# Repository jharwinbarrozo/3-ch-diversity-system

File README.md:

This is an Arduino code for a Wemos D1 board (ESP8266 chip), coupled to 3 LM1881 video sync separators, and a MAX4545 video switch.
Compared to the popular RSSI-based systems, the advantages a video-based diversity are:
- No need to open the receivers to get the RSSI [Receiver Signal Strength indication] signals. You just have to plug in your different receivers, and they can be of different types.
- There is no need to calibrate the RSSi signals of the different receivers (this is often the tricky part).
- It is also frequent to get a strongly distorted image, while the RSSI is high.
- When the reception level is low (flying far for instance), some receivers have RSSI close to zero, although the image is still viewable. In that case an RSSI-based system is not really efficient.

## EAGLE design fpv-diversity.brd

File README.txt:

l1m          = Top layer
l2m          = Bottom layer
ss1          = Top silkscreen
sm1          = Top soldermask
sm2          = Bottom soldermask
outline      = Board outline
drill        = Plated holes Excellon file
drillnpt     = Non-Plated holes Excellon file
XYRS.csv     = Parts placement file
pcb.cad      = PCBWeb Project file

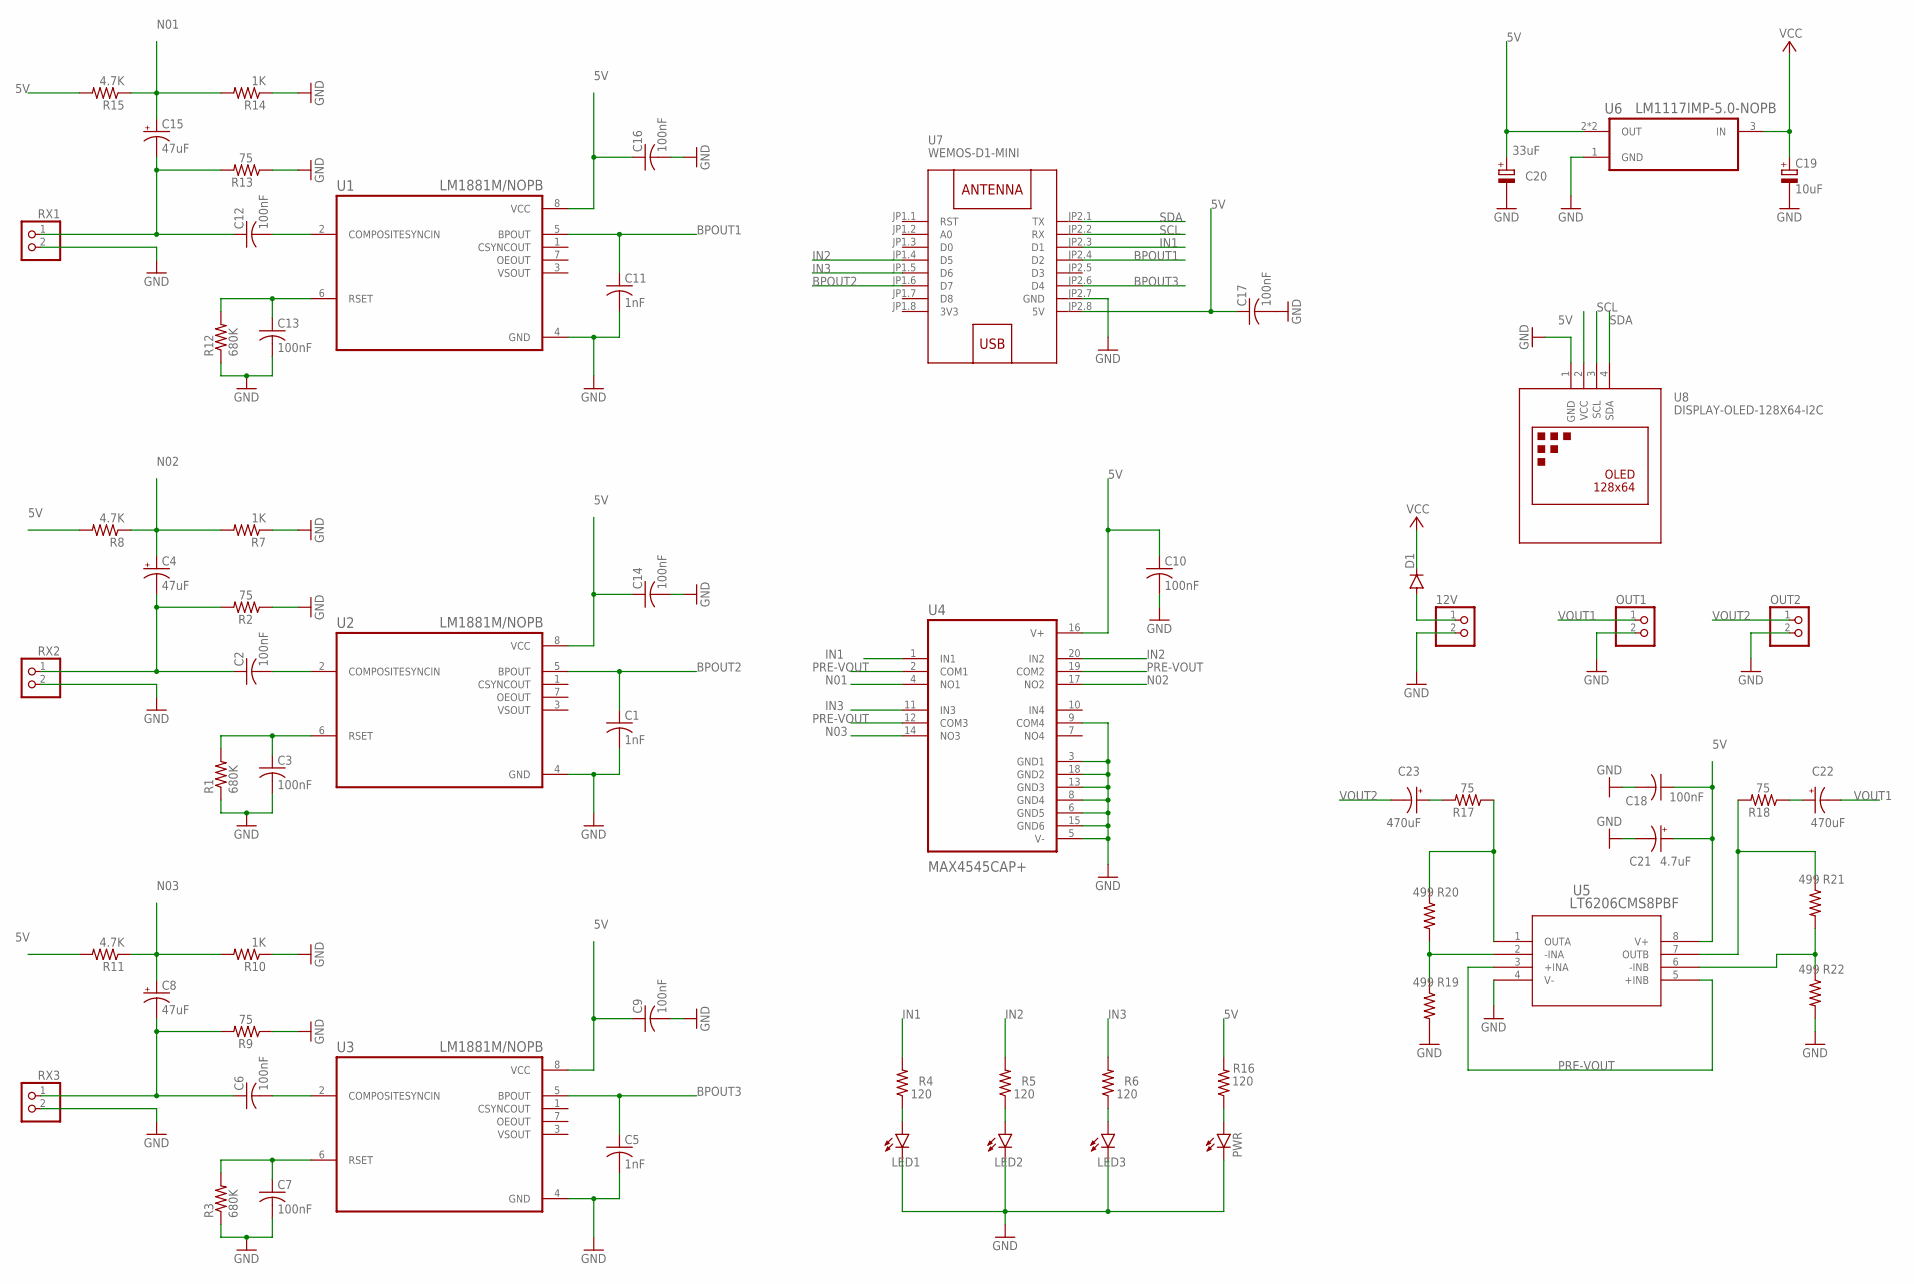
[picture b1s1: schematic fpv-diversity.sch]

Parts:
12V: PINHD-1X2; 1X02
C1, C5, C11: 1nF; C0603
C2, C3, C6, C7, C9, C10, C12, C13, C14, C16, C17, C18: 100nF; C0805
C4, C8, C15: 47uF; CT3216
C19: 10uF; D/7343-31W
C20: 33uF; D/7343-31W
C21: 4.7uF; CT3528
C22, C23: 470uF; UD-6,3X7,7_NICHICON
D1: DIODE-DO-214AC; DO-214AC
LED1, LED2, LED3: LEDCHIPLED_0603; CHIPLED_0603
OUT1, OUT2: PINHD-1X2; 1X02
PWR: LEDCHIPLED_0603; CHIPLED_0603
R1, R3, R12: 680K; R0805
R2, R9, R13, R17, R18: 75; R0805
R4, R5, R6, R16: 120; R0603
R7, R10, R14: 1K; R0805
R8, R11, R15: 4.7K; R0805
R19, R20, R21, R22: 499; R1206
RX1, RX2, RX3: PINHD-1X2; 1X02
U1, U2, U3: LM1881M/NOPB; SOIC127P599X175-8N
U4: MAX4545CAP+; SOP65P777X199-20N
U5: LT6206CMS8PBF; MSOP-8_MS
U6: LM1117IMP-5.0-NOPB; SOT230P700X180-4N
U7: WEMOS-D1-MINI
U8: DISPLAY-OLED-128X64-I2C

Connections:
3V3: U7.JP1.8 (3V3)
5V: C9.1, C10.1, C14.1, C16.1, C17.1, C18.1, C20.+, C21.+, R8.2, R11.2, R15.2, R16.2, U1.8 (VCC), U2.8 (VCC), U3.8 (VCC), U4.16 (V+), U5.8 (V+), U6.2 (OUT), U6.4 (OUT), U7.JP2.8 (5V), U8.2 (VCC)
BPOUT1: C11.1, U1.5 (BPOUT), U7.JP2.4 (D2)
BPOUT2: C1.1, U2.5 (BPOUT), U7.JP1.6 (D7)
BPOUT3: C5.1, U3.5 (BPOUT), U7.JP2.6 (D4)
GND: 12V.2, C1.2, C3.2, C5.2, C7.2, C9.2, C10.2, C11.2, C13.2, C14.2, C16.2, C17.2, C18.2, C19.-, C20.-, C21.-, LED1.C, LED2.C, LED3.C, OUT1.2, OUT2.2, PWR.C, R1.1, R2.1, R3.1, R7.1, R9.1, R10.1, R12.1, R13.1, R14.1, R19.2, R22.2, RX1.2, RX2.2, RX3.2, U1.4 (GND), U2.4 (GND), U3.4 (GND), U4.3 (GND1), U4.5 (V-), U4.6 (GND5), U4.8 (GND4), U4.9 (COM4), U4.13 (GND3), U4.15 (GND6), U4.18 (GND2), U5.4 (V-), U6.1 (GND), U7.JP2.7 (GND), U8.1 (GND)
IN1: R4.2, U4.1 (IN1), U7.JP2.3 (D1)
IN2: R5.2, U4.20 (IN2), U7.JP1.4 (D5)
IN3: R6.2, U4.11 (IN3), U7.JP1.5 (D6)
N01: C15.+, R14.2, R15.1, U4.4 (NO1)
N02: C4.+, R7.2, R8.1, U4.17 (NO2)
N03: C8.+, R10.2, R11.1, U4.14 (NO3)
unnamed: C7.1, R3.2, U3.6 (RSET)
unnamed: C3.1, R1.2, U2.6 (RSET)
unnamed: C2.2, U2.2 (COMPOSITESYNCIN)
unnamed: PWR.A, R16.1
unnamed: C6.2, U3.2 (COMPOSITESYNCIN)
unnamed: 12V.1, D1.A
unnamed: LED1.A, R4.1
unnamed: LED2.A, R5.1
unnamed: LED3.A, R6.1
unnamed: C13.1, R12.2, U1.6 (RSET)
unnamed: C12.2, U1.2 (COMPOSITESYNCIN)
unnamed: R19.1, R20.2, U5.2 (-INA)
unnamed: R18.2, R21.1, U5.7 (OUTB)
unnamed: R21.2, R22.1, U5.6 (-INB)
unnamed: R17.1, R20.1, U5.1 (OUTA)
unnamed: C22.+, R18.1
unnamed: C23.+, R17.2
PRE-VOUT: U4.2 (COM1), U4.12 (COM3), U4.19 (COM2), U5.3 (+INA), U5.5 (+INB)
SCL: U7.JP2.2 (RX), U8.3 (SCL)
SDA: U7.JP2.1 (TX), U8.4 (SDA)
VCC: C19.+, D1.C, U6.3 (IN)
VID1: C12.1, C15.-, R13.2, RX1.1
VID2: C2.1, C4.-, R2.2, RX2.1
VID3: C6.1, C8.-, R9.2, RX3.1
VOUT1: C22.-, OUT1.1
VOUT2: C23.-, OUT2.1

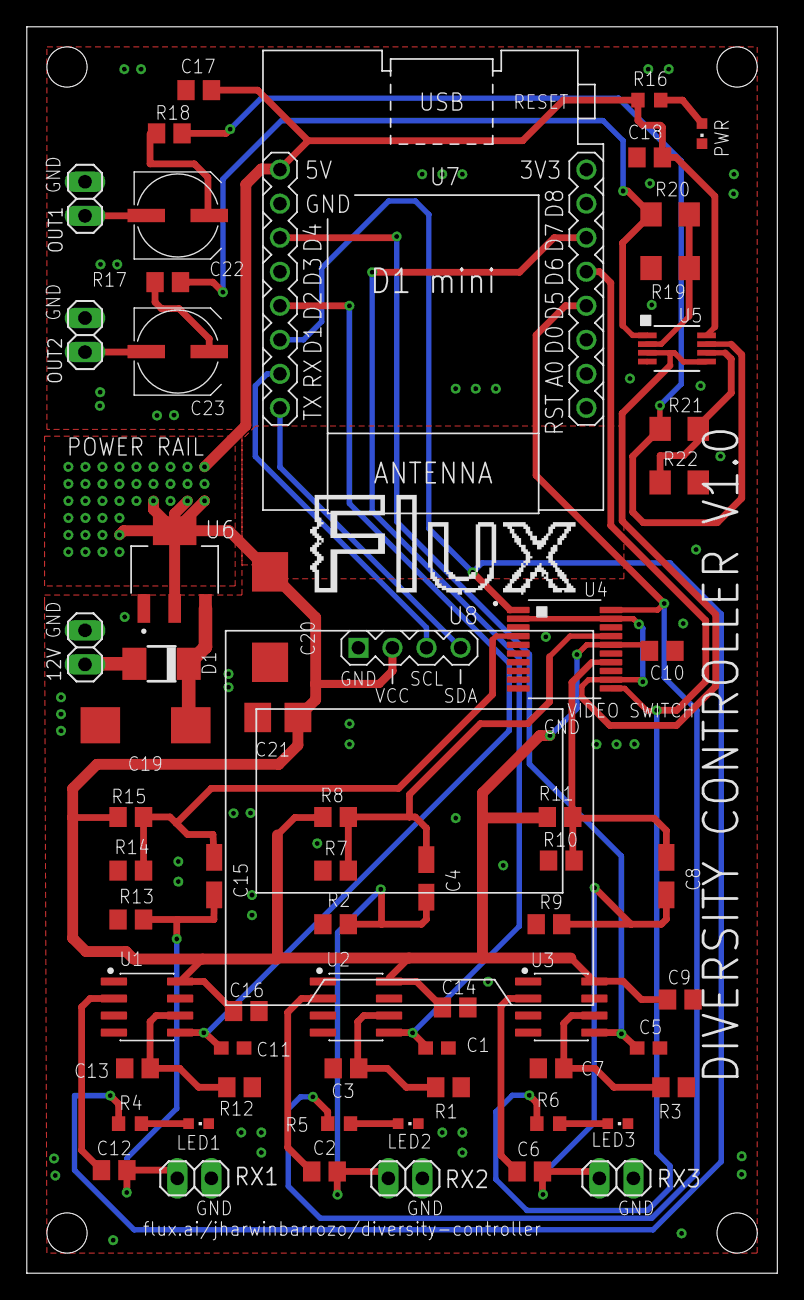
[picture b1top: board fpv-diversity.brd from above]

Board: 2 copper layers, 56.0 x 93.0 mm, 64 parts (0 on the bottom side), 37 nets.

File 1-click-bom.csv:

References,Qty,Description,Manufacturer,MPN,Digikey,Mouser,RS,Newark,Farnell
"LED1, LED2, LED3",3,SMD LED GREEN 0603,Broadcom,HSMG-C190,516-1425-1-ND,630HSMGC190,450985,,2497374
"12V, OUT1, OUT2, RX1, RX2, RX3",6,PIN HEADER VERT 2 POS,,M20-9990246,952-2262-ND,855M209990246,7457065,,1022247
"C2, C3, C6, C7, C9, C10, C12, C13, C14, C16, C17, C18",12,100nF 0805 X7R,AVX,08053C104KAT2A,311-1140-6-ND,603CC805KRX7R9BB104,6197992,,3019949
C19,1,10uF 35V Tantalum 7343,Vishay,293D106X0035D2TE3,718-1046-6-ND,74293D106X0035D2TE3,1360314,,2777998
"R7, R10, R14",3,1K 0805,Yageo,RC0805JR-071KL,311-1.00KCRCT-ND,603RC0805FR071KL,7409063,,2303550
"C1, C5, C11",3,1nF 0603 X7R,Yageo,CC0603KRX7R9BB102,399-1082-6-ND,603CC603KRX7R9BB102,2644551,,1414608
C20,1,33uF tantalum 7343,Vishay,293D336X9010D2TE3,478-4111-1-ND,74293D336X9016D2TE3,6844089,,1754190
"R8, R11, R15",3,4.7K 0805,Vishay,CRCW08054K70FKEA,P16893CT-ND,667ERJP6WF4701V,7217801,,2253928
C21,1,4.7uf  tantalum 3528,Vishay,293D475X9010B2TE3,718-1147-6-ND,74293D475X9025B2TE3,6844130,,1754215
"R4, R5, R6, R16",4,120 0603,KOA Speer,SG73P1JTTD1200F,311-120HRDKR-ND,603RC0603FR07120RL,566406,,2134805
"C22, C23",2,"470uF SMD,6.3x7.7mm Aluminum Electrolytic",Panasonic,EEEFTA471XAP,P15094TR-ND,667EEEFTA471XAP,,,2065963
"C4, C8, C15",3,47uF SMD TANTALUM 3216,AVX,F931A476KAA,478-9009-1-ND,581TLJA476M010R0600,1442515,,1658411
"R19, R20, R21, R22",4,499 1206,Panasonic,ERA8AEB4990V,P499BCDKR-ND,667ERA8AEB4990V,8280926,,2095153
"R1, R3, R12",3,680K 0805,TE Connectivity,CRGCQ0805F680K,A129783CT-ND,667ERJP06F6803V,1062967,,2861556
"R2, R9, R13, R17, R18",5,75 0805,TE Connectivity,CRG0805F75R,A126386CT-ND,603RC0805FR0775RL,8667480,,3496096
U6,1,5V Voltage Regulator,,LM1117IMP-5.0-NOPB,LM1117IMP-5.0/NOPBDKR-ND,926LM1117IMP5.0NOPB,5358641,,3122018
"U1, U2, U3",3,Video Sync Separator 8-SOIC 0 to 70,,LM1881M/NOPB,LM1881M/NOPB-ND,926LM1881M/NOPB,5361237,,3006923
U5,1,LT6206CMS8PBF,,LT6206CMS8PBF,LT6206CMS8#PBF-ND,584LT6206CMS8#PBF,,,
U4,1,Video Switch IC 4 Channel 20-SSOP,,MAX4545CAP+,MAX4545CAP+-ND,700MAX4545CAP,1897119,,2518608
U$1,1,WEMOS D1 mini: Mini Wi-Fi Board based on ESP-8266 device,,WEMOS-D1-MINI,,,,,
PWR,1,SMD LED RED 0603,Everlight,19-217/R6C-AL1M2VY/3T,516-1420-1-ND,630HSMHC190,7166570P,,1610883
D1,1,Schottky Barrier Diodes SMA(DO-214AC),Vishay,SS14-E3/5AT,SS14-E3/5ATGICT-ND,625SS14E3/5AT,5431588,,2780103

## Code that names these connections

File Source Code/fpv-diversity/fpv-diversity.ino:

// 3 channel Video Diversity Controller

// selects the best video signal, based on the detection
// of line sync. pulses (coming from using LM1881 chpis).
// The souce with the most 'regular' pulses (in the last few hundered lines)
// is chosen.
//
// Hardware:
//    - Wemos D1 mini clone (ESP8266) running at 160Mhz
//    - Video switch: Max4545
//      (allows to commute 4 sources -- but code is here for 3 sources)
//    - 3 LM1881, to generate the line sync. pulses
//
// https://randomnerdtutorials.com/esp8266-pinout-reference-gpios/
// ====================================================================

#include <ESP8266WiFi.h>
#include "user_interface.h"

//N is the number of video lines that are averaged over to decide which video source has the highest quality
#define N 500

//Un-comment the line below in order to get some debug prints on the serial output
//#define SERIAL_DEBUG

//Pin connected to the LM1881 sync outputs (INPUTS for mcu)
#define PIN_SyncA D2  // BPOUT1
#define PIN_SyncB D7  // D3 // BPOUT2
#define PIN_SyncC D4 // D4 // BPOUT3

//Pin connected to the MAX4545 (switch) pin that selects the desired source (OUTPUT for MCU)
#define PIN_selectA D1    //IN1
#define PIN_selectB D5    //IN2
#define PIN_selectC D6   //IN3

//#define PIN_ESP_LED D4    //BUILTIN-LED = wemos d1 mini clone

// keyword "Volatile" means that this variable may be changed by a routine called by some interrupt.
volatile unsigned long lastA; // Time of the last sync signal
//volatile long periodA;// Period of the last video line, in microseconds

volatile unsigned long lastB; // Time of the last sync signal
//volatile long periodB;// Period of the last video line, in microseconds

volatile unsigned long lastC; // Time of the last sync signal
//volatile long periodC;// Period of the last video line, in microseconds

unsigned long now;

#define t0 63
//const long t0 = 63;
const long unsigned mus = t0 * N; //Period to update the selected source, in micro sec.
const long unsigned mis = mus / 1000; //same as above, in milli sec.

#define sourceA 0
#define sourceB 1
#define sourceC 2
int selected;

unsigned long lastMillis;

//-----------------------------------------------------------------
//-----------------------------------------------------------------
class ExpAverage {
  private:
    volatile float x;
    const float a, b;
  public:
    ExpAverage(int n): a(1.0f / n), b(1.0f - a) { //exponential average over the ~n previous values
      x = 0.0f;
    }
    inline float getAverage() {
      return x;
    }
    void addValue(unsigned long v) {
      x = a * v + b * x;
    }
};

//-----------------------------------------------------------------
//-----------------------------------------------------------------
ExpAverage A(N), B(N), C(N);//Average video line duration for the different sources
#ifdef SERIAL_DEBUG
ExpAverage AA(N), BB(N), CC(N);//Average video line duration for the different sources
#endif
//-----------------------------------------------------------------
//-----------------------------------------------------------------

const int CLEAR = (1 << PIN_selectA) + (1 << PIN_selectB) + (1 << PIN_selectC);
int Bin[3] = {1 << PIN_selectA , 1 << PIN_selectB, 1 << PIN_selectC};
inline void SwitchTo(int s) {
  if (selected != s) {
    selected = s;
    GPOC = CLEAR;//Clear PIN_selectA, PIN_selectB and PIN_selectC simultaneously
    GPOS = Bin[s];
  }
}

//-----------------------------------------------------------------
//-----------------------------------------------------------------
class PeriodicTask {
  private:
    os_timer_t myTimer;
    int t;
  public:
    //-----------------------------
    static void DoTask(void *pArg) {//static needed here, because below we want to pass a pointer to this member function
      const unsigned long  now = micros();
      if (now - lastA > mus) {
        //if no pulse was received since last update, put the value 'mus' into the average
        //... so, if no pulse is received at all (disconnected cable, etc.à, the average line duration will be 'mus=N*64' (very large compared to 64) so this
        // source will not be selected.
        A.addValue(mus); lastA = now;
      }
      if (now - lastB > mus) B.addValue(mus), lastB = now;
      if (now - lastC > mus) C.addValue(mus), lastC = now;

      //Get the average deviation (from ~63 micro seconds) of the line durations
      const float avA = A.getAverage();
      const float avB = B.getAverage();
      const float avC = C.getAverage();

      if (avB < avA) {
        //The best is B or C
        if (avC < avB)
        {
          SwitchTo(sourceC);
          //Serial.println(avA); Serial.println(avB); Serial.println(avC);
        }
        else {
          SwitchTo(sourceB);
        }

      } else {//The best is A or C
        if (avA < avC)
          SwitchTo(sourceA); else {
            SwitchTo(sourceC);
            //Serial.println(avA); Serial.println(avB); Serial.println(avC);
          }
      }
    }
    //-----------------------------
    PeriodicTask () {
      os_timer_setfn(&myTimer, DoTask, NULL);
    }
    void Start(int t, bool repeat = true) {
      os_timer_arm(&myTimer, t, repeat);
    }
};
PeriodicTask T;

//--------Count---------------------------------------------------------
//-----------------------------------------------------------------
IRAM_ATTR void CountA() {
  const unsigned long  now = micros();
  const long period = now - lastA;
  lastA = now;
  A.addValue(abs(period - t0));
#ifdef SERIAL_DEBUG
  AA.addValue(period);
#endif
}
IRAM_ATTR void CountB() {
  const unsigned long now = micros();
  const long period = now - lastB;
  lastB = now;
  B.addValue(abs(period - t0));
#ifdef SERIAL_DEBUG
  BB.addValue(period);
#endif
}
IRAM_ATTR void CountC() {
  const unsigned long now = micros();
  const long period = now - lastC;
  lastC = now;
  C.addValue(abs(period - t0));
#ifdef SERIAL_DEBUG
  CC.addValue(period);
#endif
}
//-----------------------------------------------------------------
//-----------------------------------------------------------------

void setup() {
  //ESP.wdtDisable(); // To avoid some resets due to the software Watch Dog Timer

  WiFi.mode(WIFI_OFF);
  WiFi.forceSleepBegin();
#ifdef SERIAL_DEBUG
  Serial.begin(115200);
  Serial.println("Hello World.");
#endif
  lastA = 0; // Time of the last signal on sensor A
  lastB = 0; // Time of the last signal on sensor B
  lastC = 0; // Time of the last signal on sensor C

  pinMode(PIN_SyncA, INPUT);
  pinMode(PIN_SyncB, INPUT);
  pinMode(PIN_SyncC, INPUT);

  pinMode(PIN_selectA, OUTPUT);
  pinMode(PIN_selectB, OUTPUT);
  pinMode(PIN_selectC, OUTPUT);
//  pinMode(PIN_ESP_LED, OUTPUT);

  selected = sourceB;
  //Some blinking to start
  for (int i = 0; i < 3; i++) {
    SwitchTo(sourceA); delay(50);
    SwitchTo(sourceB); delay(50);
    SwitchTo(sourceC); delay(50);
  }
  //Declare 3 interrupts, to measure the duration between horizontal sync. pulses
  //on the 3 sources
  attachInterrupt(PIN_SyncA, CountA, FALLING);
  attachInterrupt(PIN_SyncB, CountB, FALLING);
  attachInterrupt(PIN_SyncC, CountC, FALLING);

  T.Start(mis, true); //Start the process that updates the selected source every 'mis' milliseconds (timer-based)
}
//-----------------------------------------------------------------
//-----------------------------------------------------------------

int z = 1;
void loop() {
  if (millis() > lastMillis + 500) {
    //ESP.wdtFeed();
    // Some blinking of the bluit-in led
//   if (z == 1) digitalWrite(PIN_ESP_LED, HIGH); else digitalWrite(PIN_ESP_LED, LOW); z = -z;
    lastMillis = millis();
#ifdef SERIAL_DEBUG
    //Prints some debug information to the serial output, every 1000 milli sec.
    Serial.print("Time: "); Serial.println(millis());
    if (selected == sourceA)     Serial.print("=>");
    Serial.print("RX1:");
    const float avA = A.getAverage();
    Serial.print(avA);
    const float avAA = AA.getAverage();
    Serial.print(" - "); Serial.println(avAA);

    if (selected == sourceB)     Serial.print("=>");
    Serial.print("RX2:");
    const float avB = B.getAverage();
    Serial.print(avB);
    const float avBB = BB.getAverage();
    Serial.print(" - "); Serial.println(avBB);

    if (selected == sourceC)     Serial.print("=>");
    Serial.print("RX3:");
    const float avC = C.getAverage();
    Serial.print(avC);
    const float avCC = CC.getAverage();
    Serial.print(" - "); Serial.println(avCC);


    Serial.println("");
#endif
  }
  yield();
}

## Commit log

2021-05-04 Rename README.txt to DETAILS.txt
2021-05-05 Gerber and bom files update
2021-05-05 Bom format update
2021-05-05 Move drill file into GerberFiles directory
2021-05-05 pcb routes correction
2021-05-06 Add eagle pcb file
2021-05-06 add eda,type,pcb_path
2021-05-15 PCB updates
2021-05-17 .brd cleanup
2021-05-18 more updates
2021-05-19 bom file and path updates
2021-05-20 Added more files
2021-05-29 refolder the source code, and remove pullup to all inputs
2021-05-30 Latest
2021-05-31 Source code is now platformio
2021-05-31 platformio.ini update
2021-05-31 Restructured the folder system to support vs code
2021-05-31 Removed upload speed
2021-05-31 build
2021-05-31 code cleanup
2021-06-01 Added nodemcu12-e environment and added an OLED display
2021-06-01 more code cleanup
2021-06-02 board gerber updates
2021-06-02 added ifdef for serial debug
2022-02-24 arranged the content of folders

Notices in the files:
parts and their libraries:
diy-modules: Released under the Creative Commons Attribution 4.0 International License: http://creativecommons.org/licenses/by/4.0
